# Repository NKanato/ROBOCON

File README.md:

# ROBOCON
ロボコン用リポジトリです。<br>
2023KYOROBO：2023年度九州共同ロボコン出場時の回路及びプログラム<br>
2023HONROBO：2023年度高専ロボコン出場時の回路及びプログラム<br>
の成果物を入れています。<br>
<br><br>
# 画像
2023九州共同ロボコン

<br><br>
2023高専ロボコン

<br><br>
# ディレクトリ構成
<pre>
├─2023HONROBO(2023年高専ロボコン)
│  ├─circuits
│  │  ├─CAN_bus(CAN通信バスをまとめる用)
│  │  │  └─can_bus
│  │  │      ├─canBus_plot
│  │  │      └─can_bus-backups
│  │  ├─main_board(メイン基板)
│  │  │  ├─ESP32_Devkit_V1.pretty
│  │  │  ├─main
│  │  │  └─main_board-backups
│  │  ├─undercarriage_system(足をまわり用基板)
│  │  │  ├─undercarriage2_plot
│  │  │  └─undercarriage_system-backups
│  │  └─undercarriage_system_thread(足をまわり用基板のモタドラスレッドver)
│  │      ├─plot
│  │      └─undercarriage_system-backups
│  └─sources
│      ├─2023_HONROBO_Harvest
│      ├─2023_HONROBO_main
│      └─2023_HONROBO_Wheels
└─2023KYOROBO(2023年九州共同ロボコン)
    ├─circuits
    │  ├─nucleo_446re.pretty
    │  └─NUCLEO_F446.pretty
    └─sources
</pre>
<br><br>
# 開発環境
|          |     |
|   :-:    | --- |
| OS(PC)   | Windows 10 Pro |
| OS(マイコン) | mbed-os 5.15.7, 6.13.0 |
| IDE      | Arm Keil Studio |
| HARD     | NUCLEO-F446RE, NUCLEO-F303K8 |
| LANG     | C++ |

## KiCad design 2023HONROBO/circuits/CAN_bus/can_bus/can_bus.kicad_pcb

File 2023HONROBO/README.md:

# 概要
2023年高専ロボコンで製作したロボットを制御するための回路とソースコードです。

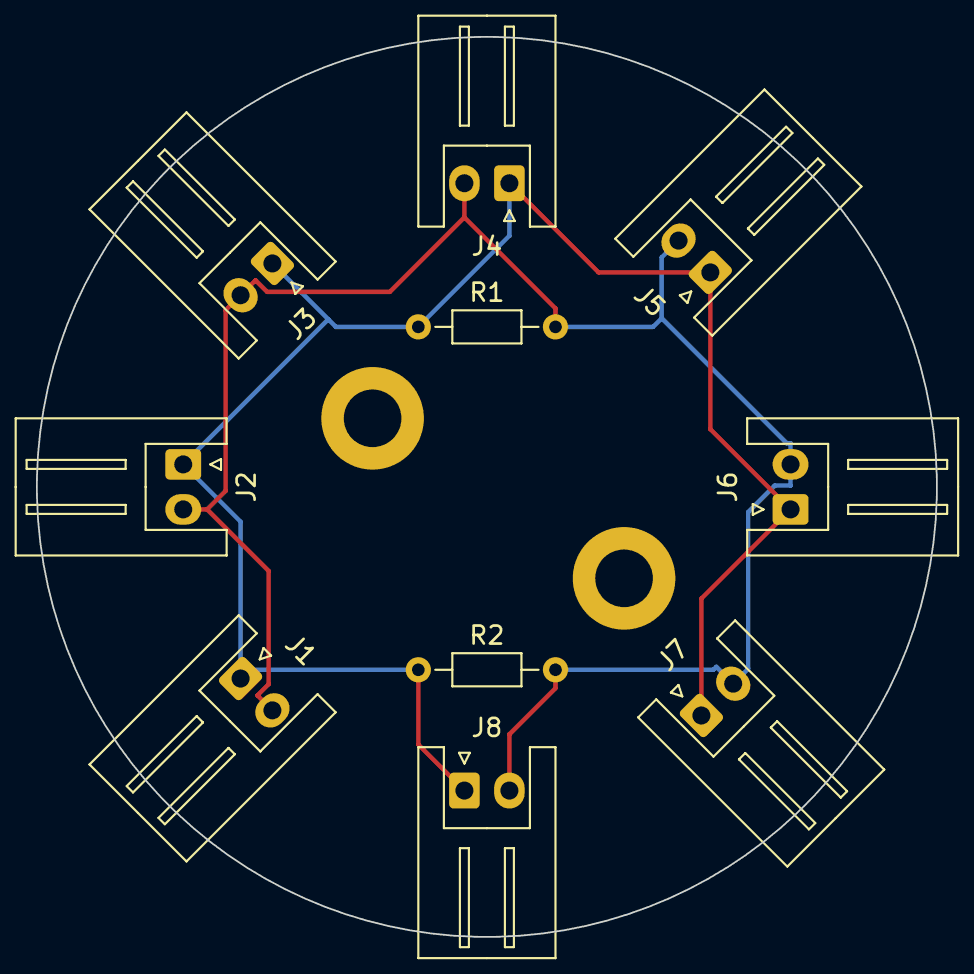
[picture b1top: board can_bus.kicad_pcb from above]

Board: 2 copper layers, 50.0 x 50.0 mm, 12 parts (0 on the bottom side), 2 nets.

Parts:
H1, H2: MountingHole; MountingHole_3.2mm_M3_ISO7380_Pad
J1, J2, J3, J4, J5, J6, J7, J8: Conn_01x02_Female; JST_XH_S2B-XH-A_1x02_P2.50mm_Horizontal
R1, R2: R; R_Axial_DIN0204_L3.6mm_D1.6mm_P7.62mm_Horizontal

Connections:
unnamed: J1.1, J2.1, J3.1, J4.1, J5.1, J6.1, J7.1, J8.1, R1.1, R2.1
unnamed: J1.2, J2.2, J3.2, J4.2, J5.2, J6.2, J7.2, J8.2, R1.2, R2.2

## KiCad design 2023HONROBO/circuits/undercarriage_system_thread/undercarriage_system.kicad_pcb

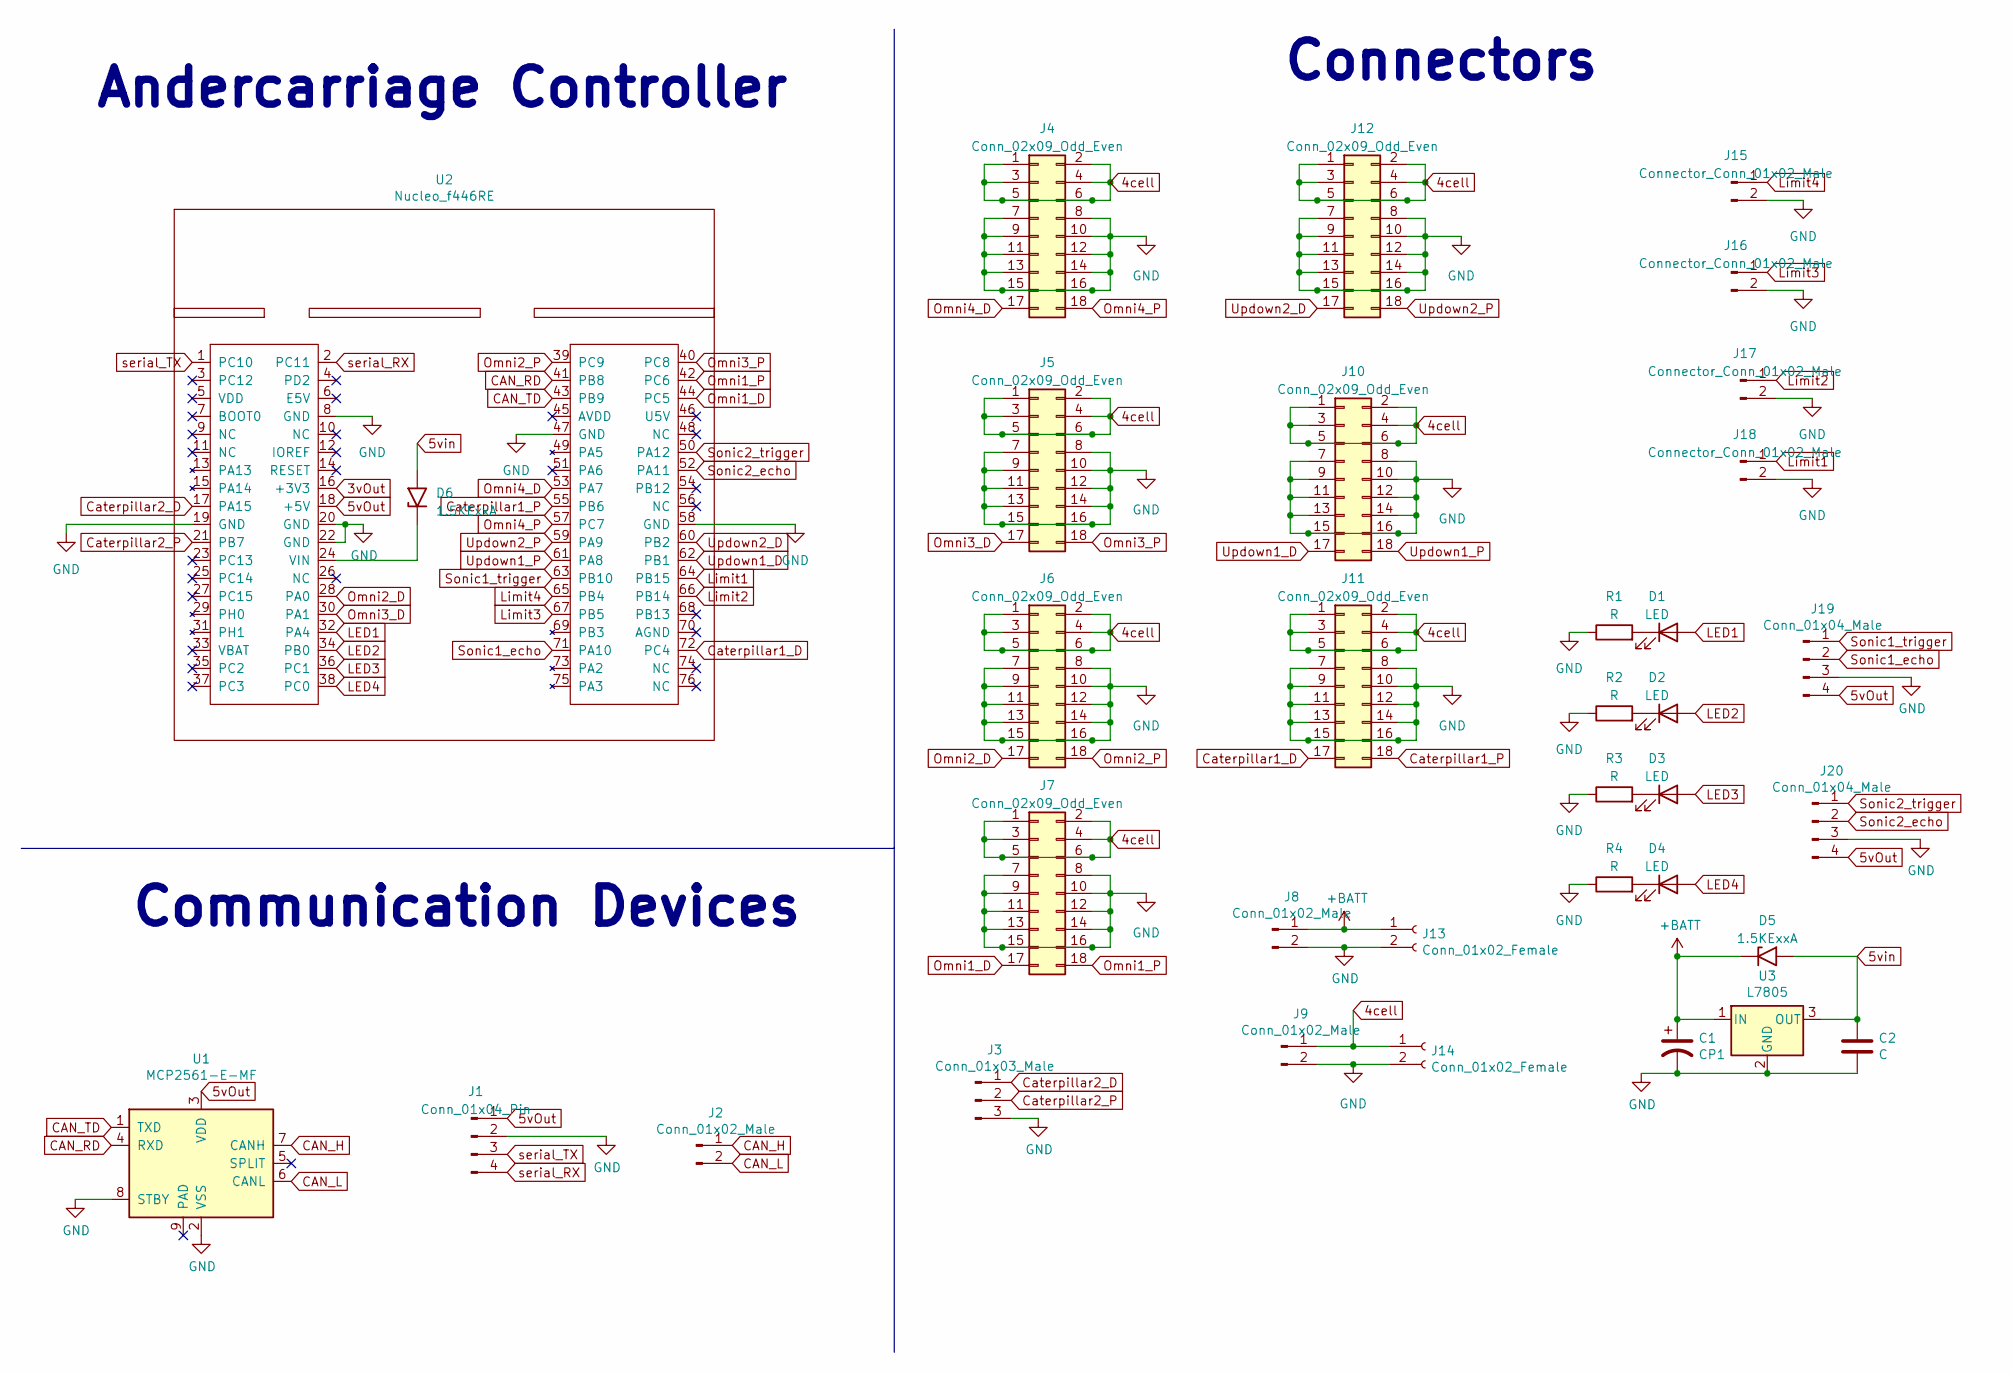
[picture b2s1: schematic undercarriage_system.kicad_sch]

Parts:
C1: CP1; CP_Radial_D6.3mm_P2.50mm
C2: C; C_Axial_L3.8mm_D2.6mm_P7.50mm_Horizontal
D1, D2, D3, D4: LED; LED_D3.0mm
D5, D6: 1.5KExxA; D_A-405_P7.62mm_Horizontal
J1: Conn_01x04_Pin; JST_XH_S4B-XH-A_1x04_P2.50mm_Horizontal
J2: Conn_01x02_Male; JST_XH_S2B-XH-A_1x02_P2.50mm_Horizontal
J3: Conn_01x03_Male; JST_XH_S3B-XH-A_1x03_P2.50mm_Horizontal
J4, J5, J6, J7, J10, J11, J12: Conn_02x09_Odd_Even; PinSocket_2x09_P2.54mm_Vertical
J8, J9: Conn_01x02_Male; Connector_T_Male
J13, J14: Conn_01x02_Female; Connector_T_Female
J15, J16, J17, J18: Connector_Conn_01x02_Male; JST_XH_S2B-XH-A_1x02_P2.50mm_Horizontal
J19, J20: Conn_01x04_Male; JST_XH_S4B-XH-A_1x04_P2.50mm_Horizontal
R1, R2, R3, R4: R; R_Axial_DIN0204_L3.6mm_D1.6mm_P7.62mm_Horizontal
U1: MCP2561-E-MF; DIP-8_W7.62mm_Socket
U2: Nucleo_f446RE; Nucleof446re
U3: L7805; NJM7805FA

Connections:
3vOut: U2.16 (+3V3)
4cell: J4.1, J4.2, J4.3, J4.4, J4.5, J4.6, J5.1, J5.2, J5.3, J5.4, J5.5, J5.6, J6.1, J6.2, J6.3, J6.4, J6.5, J6.6, J7.1, J7.2, J7.3, J7.4, J7.5, J7.6, J9.1, J10.1, J10.2, J10.3, J10.4, J10.5, J10.6, J11.1, J11.2, J11.3, J11.4, J11.5, J11.6, J12.1, J12.2, J12.3, J12.4, J12.5, J12.6, J14.1
5vOut: J1.1, J19.4, J20.4, U1.3 (VDD), U2.18 (+5V)
5vin: C2.1, D5.2 (A2), D6.2 (A2), U3.3 (OUT)
+BATT: C1.1, D5.1 (A1), J8.1, J13.1, U3.1 (IN)
CAN_RD: U1.4 (RXD), U2.41 (PB8)
CAN_TD: U1.1 (TXD), U2.43 (PB9)
Caterpillar1_D: J11.17, U2.72 (PC4)
Caterpillar1_P: J11.18, U2.55 (PB6)
Caterpillar2_D: J3.1, U2.17 (PA15)
Caterpillar2_P: J3.2, U2.21 (PB7)
GND: C1.2, C2.2, J1.2, J3.3, J4.7, J4.8, J4.9, J4.10, J4.11, J4.12, J4.13, J4.14, J4.15, J4.16, J5.7, J5.8, J5.9, J5.10, J5.11, J5.12, J5.13, J5.14, J5.15, J5.16, J6.7, J6.8, J6.9, J6.10, J6.11, J6.12, J6.13, J6.14, J6.15, J6.16, J7.7, J7.8, J7.9, J7.10, J7.11, J7.12, J7.13, J7.14, J7.15, J7.16, J8.2, J9.2, J10.7, J10.8, J10.9, J10.10, J10.11, J10.12, J10.13, J10.14, J10.15, J10.16, J11.7, J11.8, J11.9, J11.10, J11.11, J11.12, J11.13, J11.14, J11.15, J11.16, J12.7, J12.8, J12.9, J12.10, J12.11, J12.12, J12.13, J12.14, J12.15, J12.16, J13.2, J14.2, J15.2, J16.2, J17.2, J18.2, J19.3, J20.3, R1.1, R2.1, R3.1, R4.1, U1.2 (VSS), U1.8 (STBY), U2.8 (GND), U2.19 (GND), U2.20 (GND), U2.22 (GND), U2.47 (GND), U2.58 (GND), U3.2 (GND)
LED1: D1.2 (A), U2.32 (PA4)
LED2: D2.2 (A), U2.34 (PB0)
LED3: D3.2 (A), U2.36 (PC1)
LED4: D4.2 (A), U2.38 (PC0)
Limit1: J18.1, U2.64 (PB15)
Limit2: J17.1, U2.66 (PB14)
Limit3: J16.1, U2.67 (PB5)
Limit4: J15.1, U2.65 (PB4)
unnamed: D1.1 (K), R1.2
unnamed: D2.1 (K), R2.2
unnamed: D3.1 (K), R3.2
unnamed: D4.1 (K), R4.2
unnamed: D6.1 (A1), U2.24 (VIN)
Omni1_D: J7.17, U2.44 (PC5)
Omni1_P: J7.18, U2.42 (PC6)
Omni2_D: J6.17, U2.28 (PA0)
Omni2_P: J6.18, U2.39 (PC9)
Omni3_D: J5.17, U2.30 (PA1)
Omni3_P: J5.18, U2.40 (PC8)
Omni4_D: J4.17, U2.53 (PA7)
Omni4_P: J4.18, U2.57 (PC7)
Sonic1_echo: J19.2, U2.71 (PA10)
Sonic1_trigger: J19.1, U2.63 (PB10)
Sonic2_echo: J20.2, U2.52 (PA11)
Sonic2_trigger: J20.1, U2.50 (PA12)
Updown1_D: J10.17, U2.62 (PB1)
Updown1_P: J10.18, U2.61 (PA8)
Updown2_D: J12.17, U2.60 (PB2)
Updown2_P: J12.18, U2.59 (PA9)
serial_RX: J1.4, U2.2 (PC11)
serial_TX: J1.3, U2.1 (PC10)

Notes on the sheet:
Connectors
Communication Devices
Andercarriage Controller

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
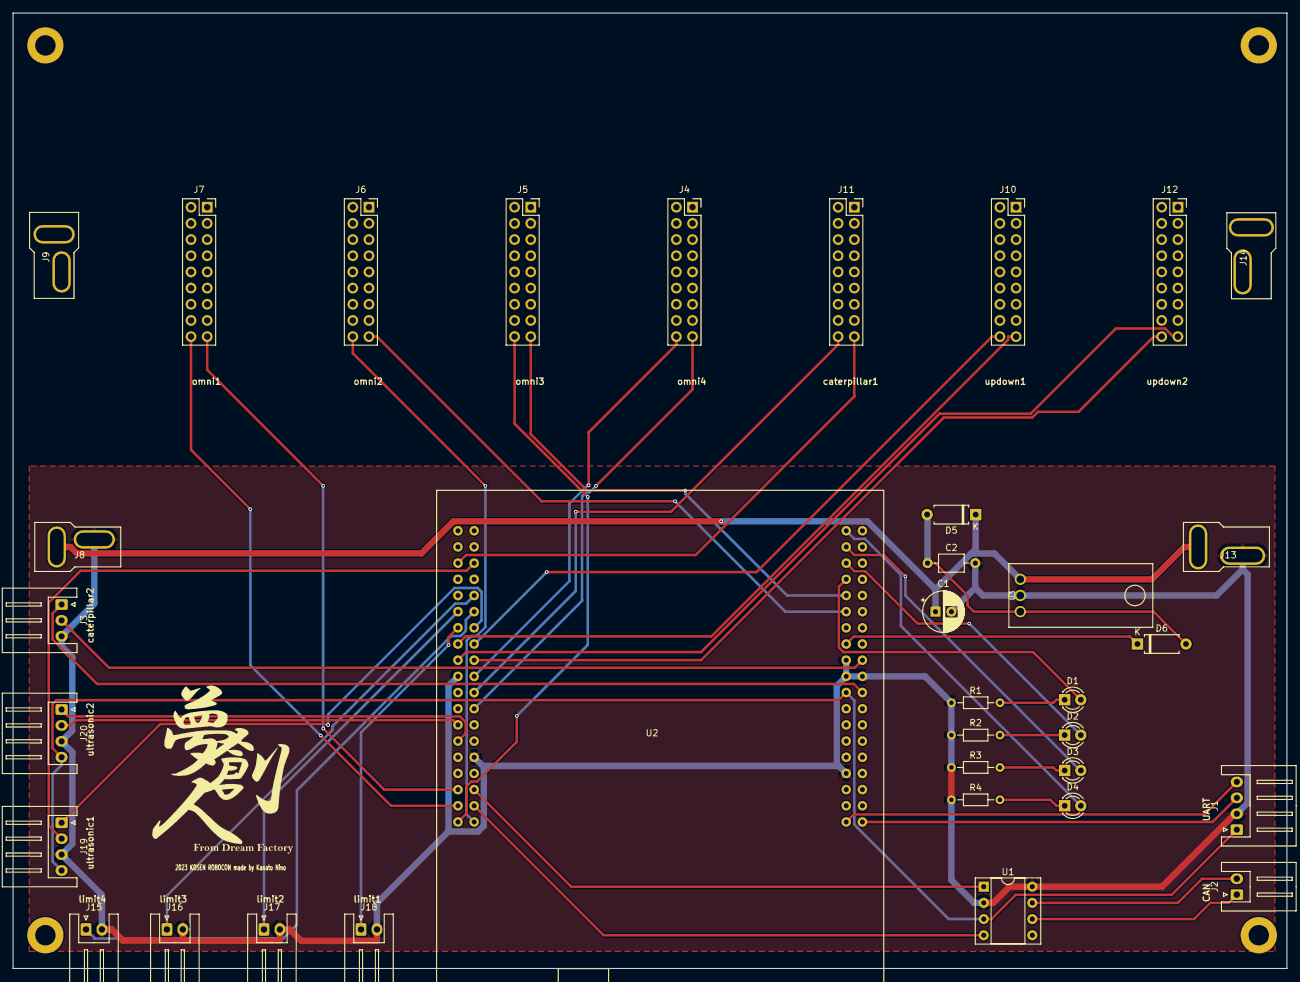
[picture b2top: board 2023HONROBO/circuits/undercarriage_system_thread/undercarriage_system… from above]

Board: 2 copper layers, 200.0 x 150.0 mm, 35 parts (0 on the bottom side), 44 nets.

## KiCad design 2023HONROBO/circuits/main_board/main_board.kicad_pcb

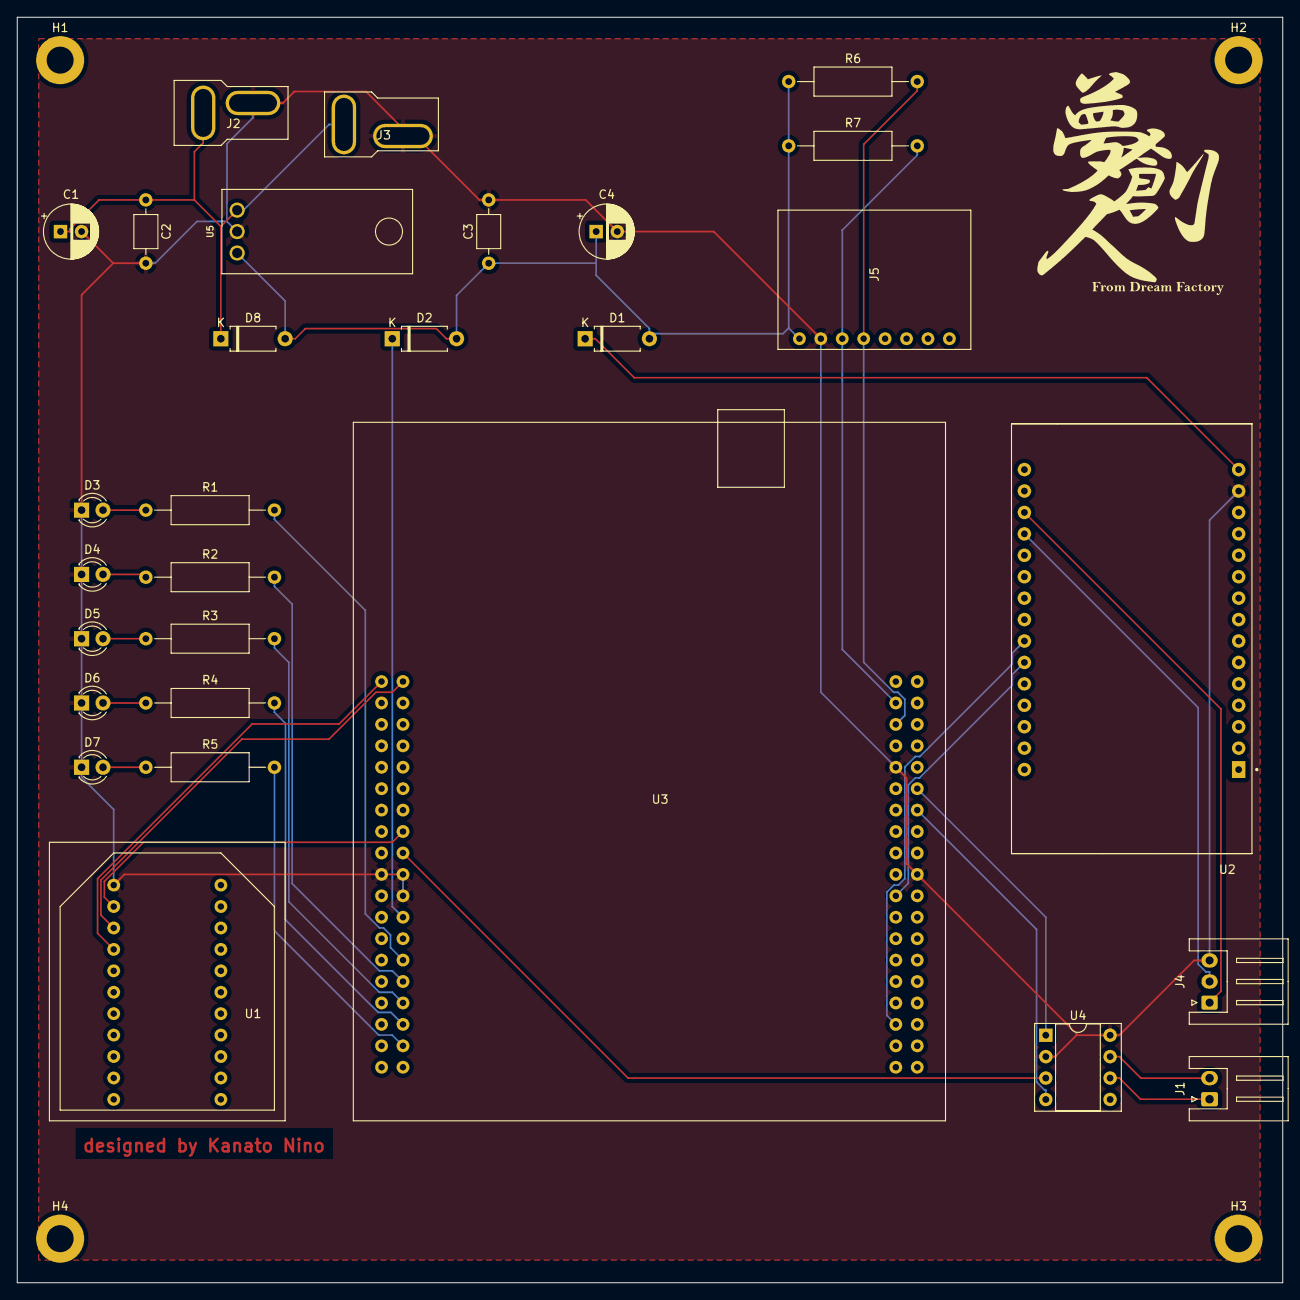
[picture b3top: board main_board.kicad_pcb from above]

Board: 2 copper layers, 150.0 x 150.0 mm, 33 parts (0 on the bottom side), 29 nets.

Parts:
C1, C4: CP1; CP_Radial_D6.3mm_P2.50mm
C2, C3: C; C_Axial_L3.8mm_D2.6mm_P7.50mm_Horizontal
D1, D2, D8: 1.5KExxA; D_A-405_P7.62mm_Horizontal
D3, D4, D5, D6, D7: LED; LED_D3.0mm
H1, H2, H3, H4: MountingHole; MountingHole_3.2mm_M3_ISO7380_Pad
J1: Conn_01x02_Male; JST_XH_S2B-XH-A_1x02_P2.50mm_Horizontal
J2: Conn_01x02_Male; Connector_T_Male
J3: Conn_01x02_Female; Connector_T_Female
J4: Conn_01x03_Male; JST_XH_S3B-XH-A_1x03_P2.50mm_Horizontal
J5: Conn_01x08_Pin; GY=521
R1, R2, R3, R4, R5, R6, R7: R; R_Axial_DIN0309_L9.0mm_D3.2mm_P15.24mm_Horizontal
U1: xbeepros1; xbee_pro_s1
U2: ESP32_3-Pin; MODULE_ESP32_DEVKIT_V1
U3: Nucleo_f446RE; Nucleof446re
U4: MCP2561-E-MF; DIP-8_W7.62mm_Socket
U5: L7805; NJM7805FA

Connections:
3vOut: U1.2 (3.3v), U3.16 (+3V3)
5vOut: U3.18 (+5V), U4.3 (VDD)
5vin: C3.1, C4.1, D1.2 (A2), D2.2 (A2), D8.2 (A2), J5.1, R6.1, R7.1, U5.3 (OUT)
+BATT: C1.1, C2.1, D8.1 (A1), J2.1, J3.1, U5.1 (IN)
CAN1_RD: U3.52 (PA11), U4.4 (RXD)
CAN1_TD: U3.50 (PA12), U4.1 (TXD)
CAN_H: J1.2, U4.7 (CANH)
CAN_L: J1.1, U4.6 (CANL)
ESP32_RX: U2.24 (GPIO17), U3.71 (PA10)
ESP32_TX: U2.25 (GPIO16), U3.59 (PA9)
GND: C1.2, C2.2, C3.2, C4.2, D3.1 (K), D4.1 (K), D5.1 (K), D6.1 (K), D7.1 (K), J2.2, J3.2, J4.3, J5.2, U1.1 (gnd), U2.14 (GND), U3.19 (GND), U3.20 (GND), U3.22 (GND), U3.47 (GND), U3.58 (GND), U4.2 (VSS), U4.8 (STBY), U5.2 (GND)
I2C1_SCL: J5.3, R7.2, U3.41 (PB8)
I2C1_SDA: J5.4, R6.2, U3.43 (PB9)
LED1: R1.2, U3.28 (PA0)
LED2: R2.2, U3.30 (PA1)
LED3: R3.2, U3.32 (PA4)
LED4: R4.2, U3.34 (PB0)
LED5: R5.2, U3.36 (PC1)
unnamed: D1.1 (A1), U2.15 (5V)
unnamed: D2.1 (A1), U3.24 (VIN)
unnamed: D3.2 (A), R1.1
unnamed: D4.2 (A), R2.1
unnamed: D5.2 (A), R3.1
unnamed: D6.2 (A), R4.1
unnamed: D7.2 (A), R5.1
PS3_RX: U1.3 (out), U3.2 (PC11)
PS3_TX: U1.4 (in), U3.1 (PC10)
stop_RX: J4.2, U2.19 (RXD0)
stop_TX: J4.1, U2.18 (TXD0)

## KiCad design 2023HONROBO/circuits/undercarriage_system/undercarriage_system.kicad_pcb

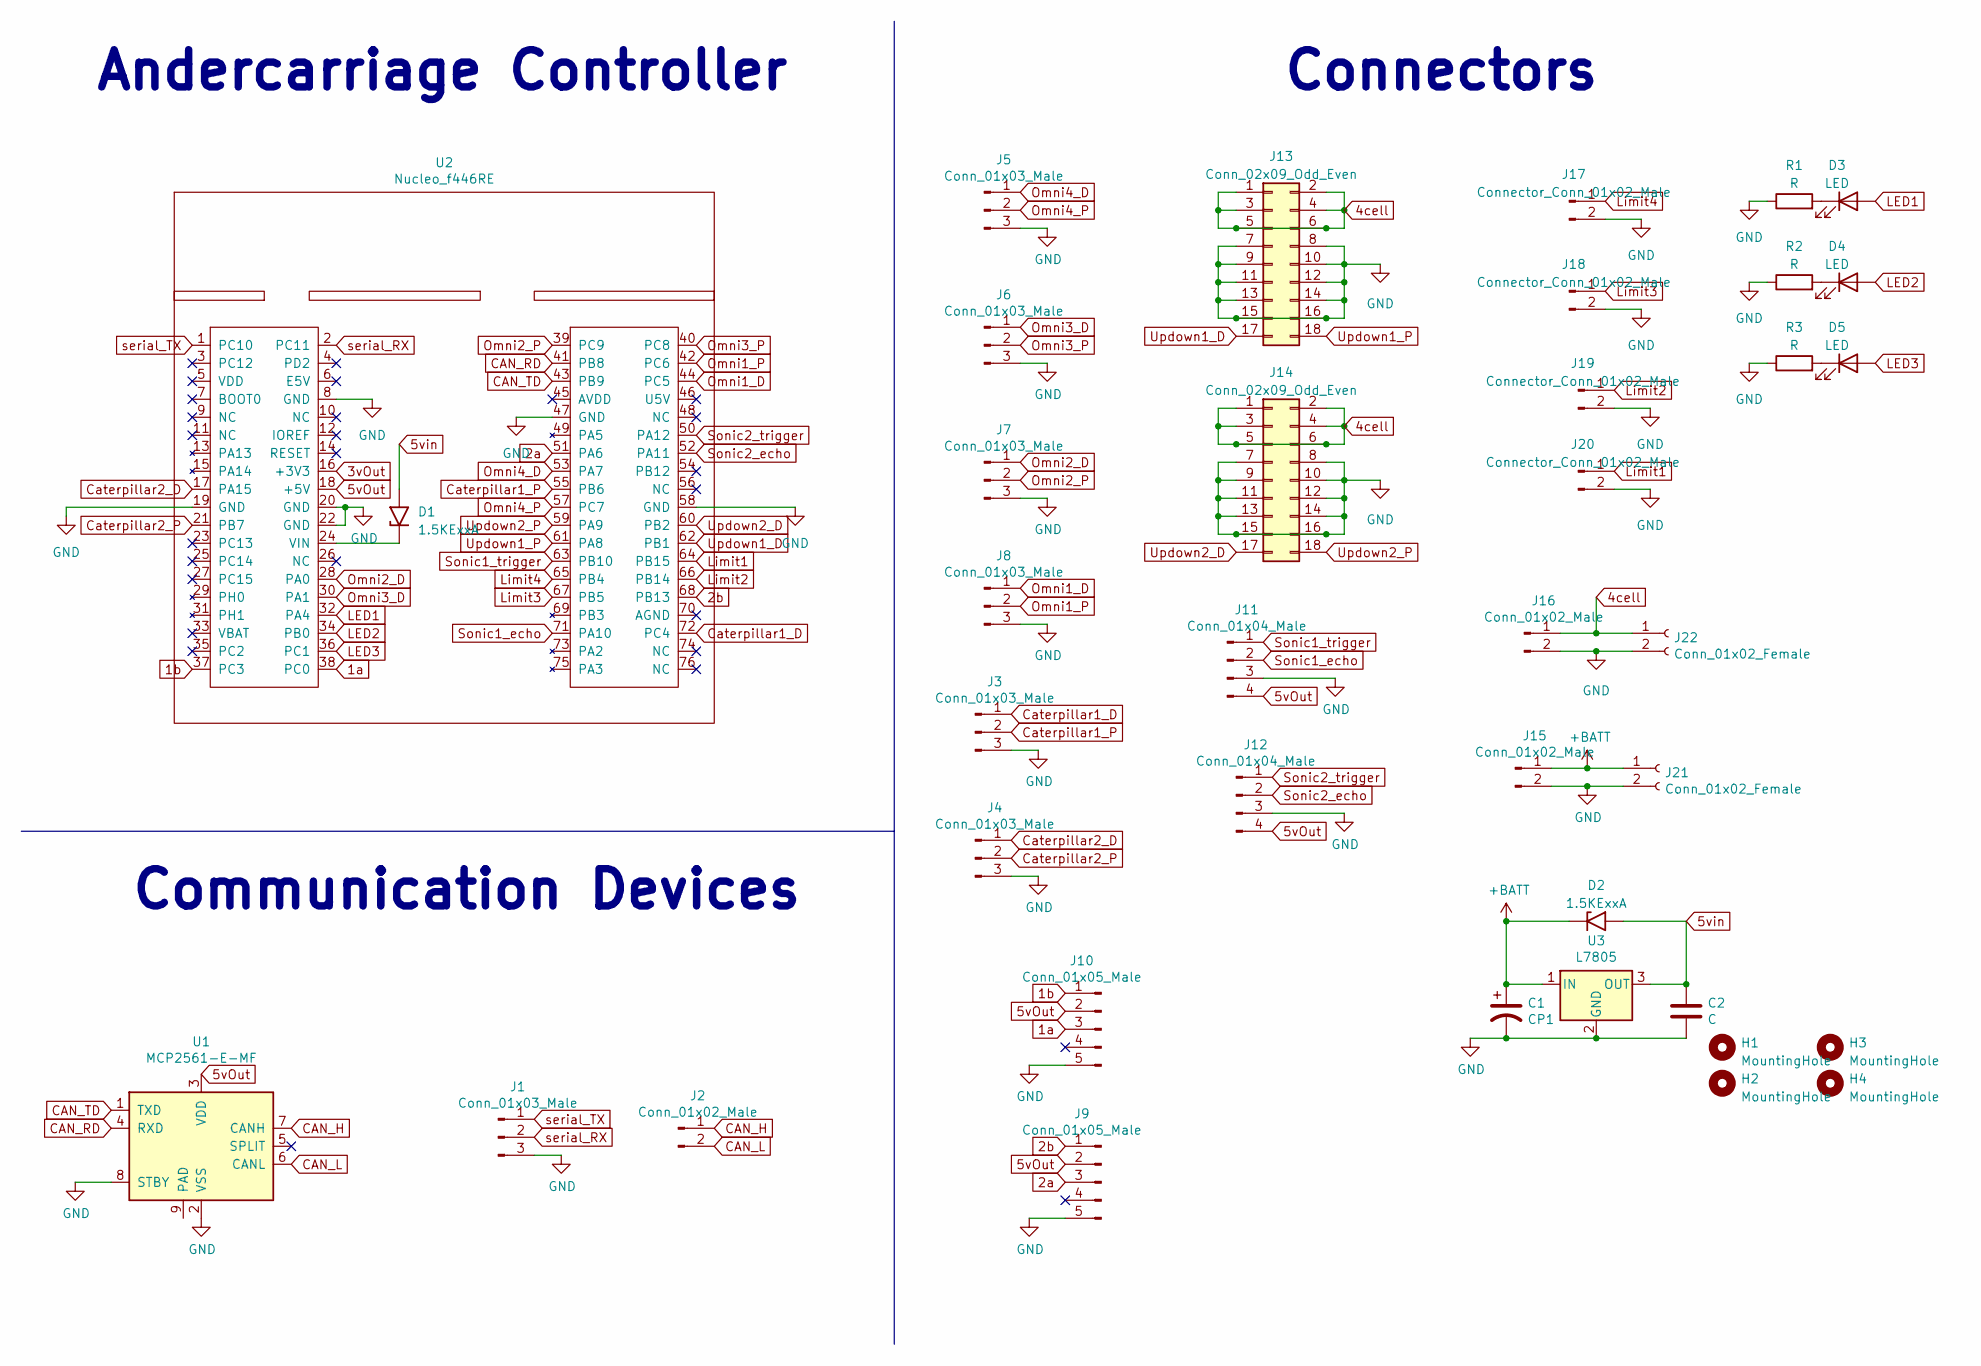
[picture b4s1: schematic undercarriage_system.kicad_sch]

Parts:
C1: CP1; CP_Radial_D6.3mm_P2.50mm
C2: C; C_Axial_L3.8mm_D2.6mm_P7.50mm_Horizontal
D1, D2: 1.5KExxA; D_A-405_P7.62mm_Horizontal
D3, D4, D5: LED; LED_D3.0mm
H1, H2, H3, H4: MountingHole; MountingHole_3.2mm_M3_ISO7380_Pad
J1, J3, J4, J5, J6, J7, J8: Conn_01x03_Male; JST_XH_S3B-XH-A_1x03_P2.50mm_Horizontal
J2: Conn_01x02_Male; JST_XH_S2B-XH-A_1x02_P2.50mm_Horizontal
J9, J10: Conn_01x05_Male; JST_XH_S5B-XH-A_1x05_P2.50mm_Horizontal
J11, J12: Conn_01x04_Male; JST_XH_S4B-XH-A_1x04_P2.50mm_Horizontal
J13, J14: Conn_02x09_Odd_Even; PinSocket_2x09_P2.54mm_Vertical
J15, J16: Conn_01x02_Male; Connector_T_Male
J17, J18, J19, J20: Connector_Conn_01x02_Male; JST_XH_S2B-XH-A_1x02_P2.50mm_Horizontal
J21, J22: Conn_01x02_Female; Connector_T_Female
R1, R2, R3: R; R_Axial_DIN0204_L3.6mm_D1.6mm_P7.62mm_Horizontal
U1: MCP2561-E-MF; DIP-8_W7.62mm_Socket
U2: Nucleo_f446RE; Nucleof446re
U3: L7805; NJM7805FA

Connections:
1a: J10.3, U2.38 (PC0)
1b: J10.1, U2.37 (PC3)
2a: J9.3, U2.51 (PA6)
2b: J9.1, U2.68 (PB13)
3vOut: U2.16 (+3V3)
4cell: J13.1, J13.2, J13.3, J13.4, J13.5, J13.6, J14.1, J14.2, J14.3, J14.4, J14.5, J14.6, J16.1, J22.1
5vOut: J9.2, J10.2, J11.4, J12.4, U1.3 (VDD), U2.18 (+5V)
5vin: C2.1, D1.2 (A2), D2.2 (A2), U3.3 (OUT)
+BATT: C1.1, D2.1 (A1), J15.1, J21.1, U3.1 (IN)
CAN_H: J2.1, U1.7 (CANH)
CAN_L: J2.2, U1.6 (CANL)
CAN_RD: U1.4 (RXD), U2.41 (PB8)
CAN_TD: U1.1 (TXD), U2.43 (PB9)
Caterpillar1_D: J3.1, U2.72 (PC4)
Caterpillar1_P: J3.2, U2.55 (PB6)
Caterpillar2_D: J4.1, U2.17 (PA15)
Caterpillar2_P: J4.2, U2.21 (PB7)
GND: C1.2, C2.2, J1.3, J3.3, J4.3, J5.3, J6.3, J7.3, J8.3, J9.5, J10.5, J11.3, J12.3, J13.7, J13.8, J13.9, J13.10, J13.11, J13.12, J13.13, J13.14, J13.15, J13.16, J14.7, J14.8, J14.9, J14.10, J14.11, J14.12, J14.13, J14.14, J14.15, J14.16, J15.2, J16.2, J17.2, J18.2, J19.2, J20.2, J21.2, J22.2, R1.1, R2.1, R3.1, U1.2 (VSS), U1.8 (STBY), U2.8 (GND), U2.19 (GND), U2.20 (GND), U2.22 (GND), U2.47 (GND), U2.58 (GND), U3.2 (GND)
LED1: D3.2 (A), U2.32 (PA4)
LED2: D4.2 (A), U2.34 (PB0)
LED3: D5.2 (A), U2.36 (PC1)
Limit1: J20.1, U2.64 (PB15)
Limit2: J19.1, U2.66 (PB14)
Limit3: J18.1, U2.67 (PB5)
Limit4: J17.1, U2.65 (PB4)
unnamed: D1.1 (A1), U2.24 (VIN)
unnamed: D3.1 (K), R1.2
unnamed: D4.1 (K), R2.2
unnamed: D5.1 (K), R3.2
Omni1_D: J8.1, U2.44 (PC5)
Omni1_P: J8.2, U2.42 (PC6)
Omni2_D: J7.1, U2.28 (PA0)
Omni2_P: J7.2, U2.39 (PC9)
Omni3_D: J6.1, U2.30 (PA1)
Omni3_P: J6.2, U2.40 (PC8)
Omni4_D: J5.1, U2.53 (PA7)
Omni4_P: J5.2, U2.57 (PC7)
Sonic1_echo: J11.2, U2.71 (PA10)
Sonic1_trigger: J11.1, U2.63 (PB10)
Sonic2_echo: J12.2, U2.52 (PA11)
Sonic2_trigger: J12.1, U2.50 (PA12)
Updown1_D: J13.17, U2.62 (PB1)
Updown1_P: J13.18, U2.61 (PA8)
Updown2_D: J14.17, U2.60 (PB2)
Updown2_P: J14.18, U2.59 (PA9)
serial_RX: J1.2, U2.2 (PC11)
serial_TX: J1.1, U2.1 (PC10)

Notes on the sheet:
Connectors
Communication Devices
Andercarriage Controller

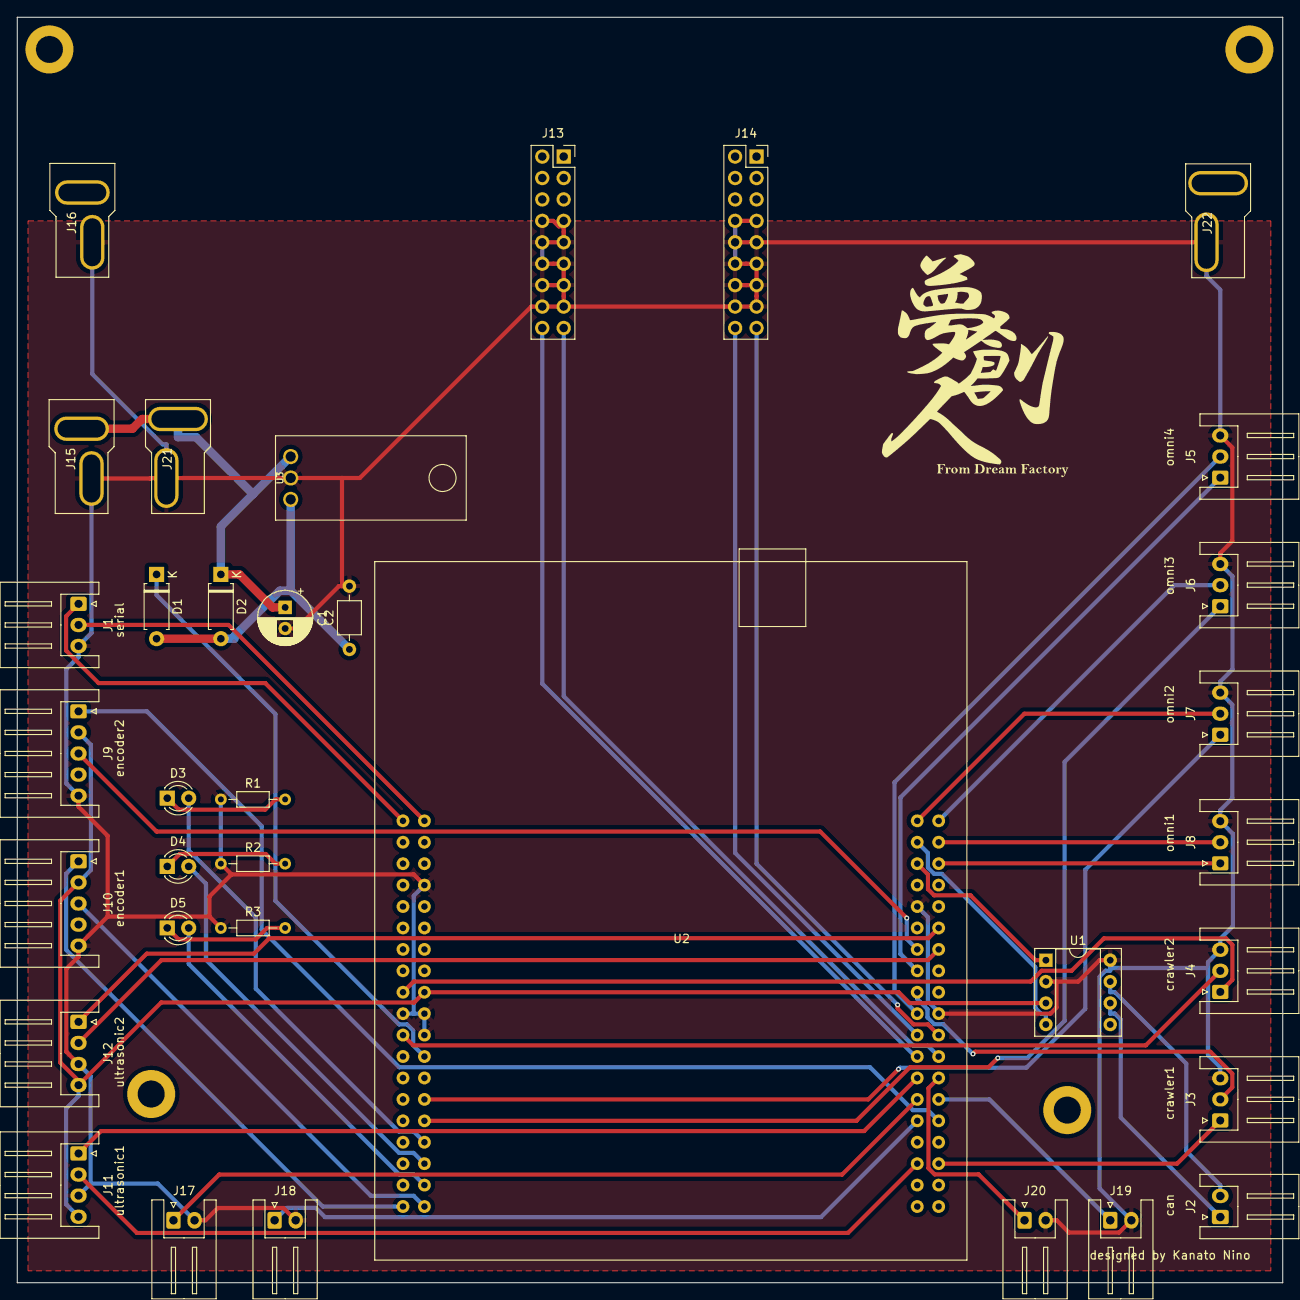
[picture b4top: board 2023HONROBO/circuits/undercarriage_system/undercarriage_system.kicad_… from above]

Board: 2 copper layers, 150.0 x 150.0 mm, 39 parts (0 on the bottom side), 46 nets.

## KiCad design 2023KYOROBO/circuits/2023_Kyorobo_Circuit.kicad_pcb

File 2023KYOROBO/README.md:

# 概要
2023年九州共同ロボコンのロボットの回路データとソースコードです。回路はエッチングで作ることを想定しています。

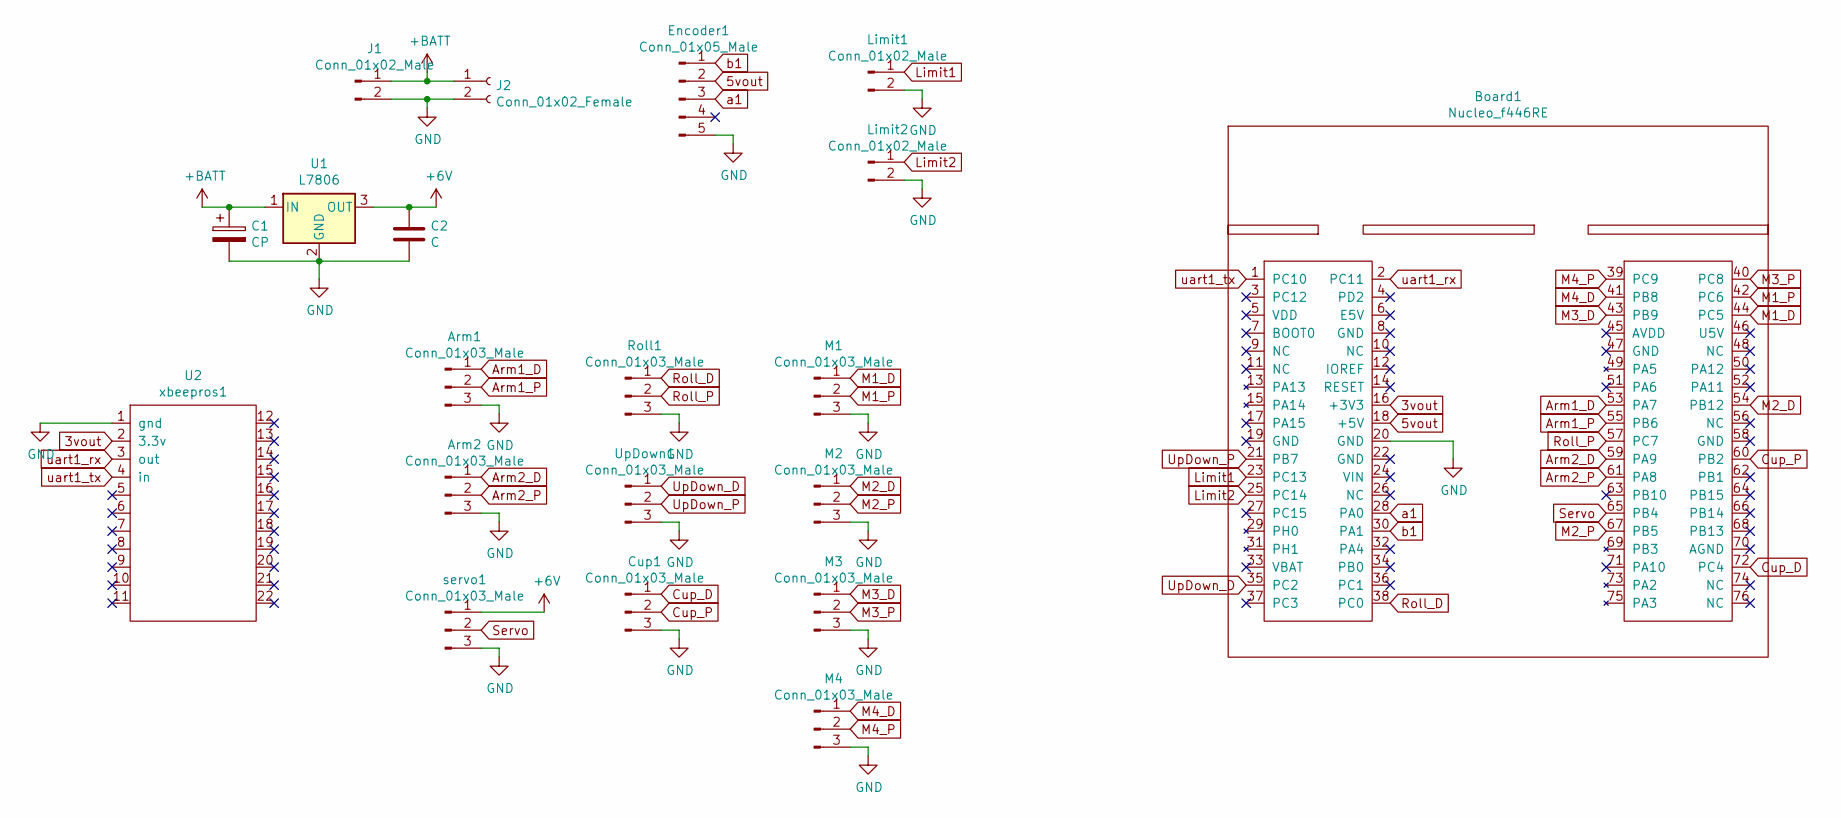
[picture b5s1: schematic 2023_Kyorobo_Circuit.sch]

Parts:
Arm1, Arm2: Conn_01x03_Male; JST_XH_S3B-XH-A-1_1x03_P2.50mm_Horizontal
Board1: Nucleo_f446RE; Nucleof446re
C1: CP; CP_Radial_D7.5mm_P2.50mm
C2: C; C_Axial_L3.8mm_D2.6mm_P7.50mm_Horizontal
Cup1: Conn_01x03_Male; JST_XH_S3B-XH-A-1_1x03_P2.50mm_Horizontal
Encoder1: Conn_01x05_Male; JST_XH_S5B-XH-A-1_1x05_P2.50mm_Horizontal
J1: Conn_01x02_Male; Connector_T_Male
J2: Conn_01x02_Female; Connector_T_Female
Limit1, Limit2: Conn_01x02_Male; JST_XH_S2B-XH-A-1_1x02_P2.50mm_Horizontal
M1, M2, M3, M4: Conn_01x03_Male; JST_XH_S3B-XH-A-1_1x03_P2.50mm_Horizontal
Roll1: Conn_01x03_Male; JST_XH_S3B-XH-A-1_1x03_P2.50mm_Horizontal
U1: L7806; NJM7805FA
U2: xbeepros1; xbee_pro_s1
UpDown1: Conn_01x03_Male; JST_XH_S3B-XH-A-1_1x03_P2.50mm_Horizontal
servo1: Conn_01x03_Male; JST_XH_S3B-XH-A-1_1x03_P2.50mm_Horizontal

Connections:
3vout: Board1.16 (+3V3), U2.2 (3.3v)
5vout: Board1.18 (+5V), Encoder1.2
+6V: C2.1, U1.3 (OUT), servo1.1
+BATT: C1.1, J1.1, J2.1, U1.1 (IN)
Arm1_D: Arm1.1, Board1.53 (PA7)
Arm1_P: Arm1.2, Board1.55 (PB6)
Arm2_D: Arm2.1, Board1.59 (PA9)
Arm2_P: Arm2.2, Board1.61 (PA8)
Cup_D: Board1.72 (PC4), Cup1.1
Cup_P: Board1.60 (PB2), Cup1.2
GND: Arm1.3, Arm2.3, Board1.20 (GND), C1.2, C2.2, Cup1.3, Encoder1.5, J1.2, J2.2, Limit1.2, Limit2.2, M1.3, M2.3, M3.3, M4.3, Roll1.3, U1.2 (GND), U2.1 (gnd), UpDown1.3, servo1.3
Limit1: Board1.23 (PC13), Limit1.1
Limit2: Board1.25 (PC14), Limit2.1
M1_D: Board1.44 (PC5), M1.1
M1_P: Board1.42 (PC6), M1.2
M2_D: Board1.54 (PB12), M2.1
M2_P: Board1.67 (PB5), M2.2
M3_D: Board1.43 (PB9), M3.1
M3_P: Board1.40 (PC8), M3.2
M4_D: Board1.41 (PB8), M4.1
M4_P: Board1.39 (PC9), M4.2
Roll_D: Board1.38 (PC0), Roll1.1
Roll_P: Board1.57 (PC7), Roll1.2
Servo: Board1.65 (PB4), servo1.2
UpDown_D: Board1.35 (PC2), UpDown1.1
UpDown_P: Board1.21 (PB7), UpDown1.2
a1: Board1.28 (PA0), Encoder1.3
b1: Board1.30 (PA1), Encoder1.1
uart1_rx: Board1.2 (PC11), U2.3 (out)
uart1_tx: Board1.1 (PC10), U2.4 (in)

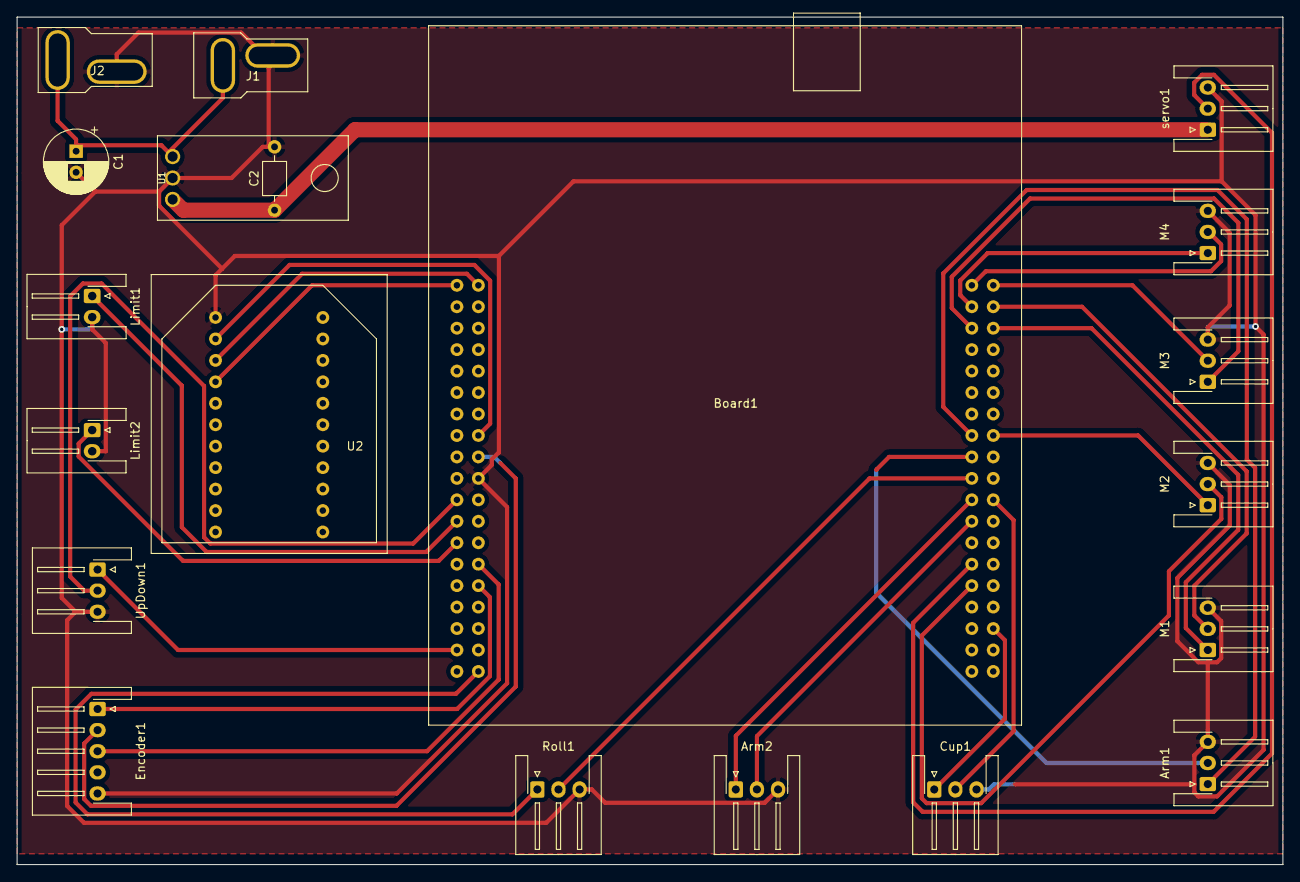
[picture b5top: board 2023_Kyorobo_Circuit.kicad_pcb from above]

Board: 2 copper layers, 149.9 x 100.3 mm, 20 parts (0 on the bottom side), 30 nets.

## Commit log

2025-09-16 2023HONROBOを追加
2025-09-22 modified readme
2025-09-23 added two images to README
